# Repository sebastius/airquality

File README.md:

# airquality
A module based air quality sensor

Will feature
* ESP32
* BME280 for temperature, relative humidity and pressure
* PMS7003 for PM2.5 particles
* MH-Z19 for CO2

(and will strive for expandability with several standarized connectors)

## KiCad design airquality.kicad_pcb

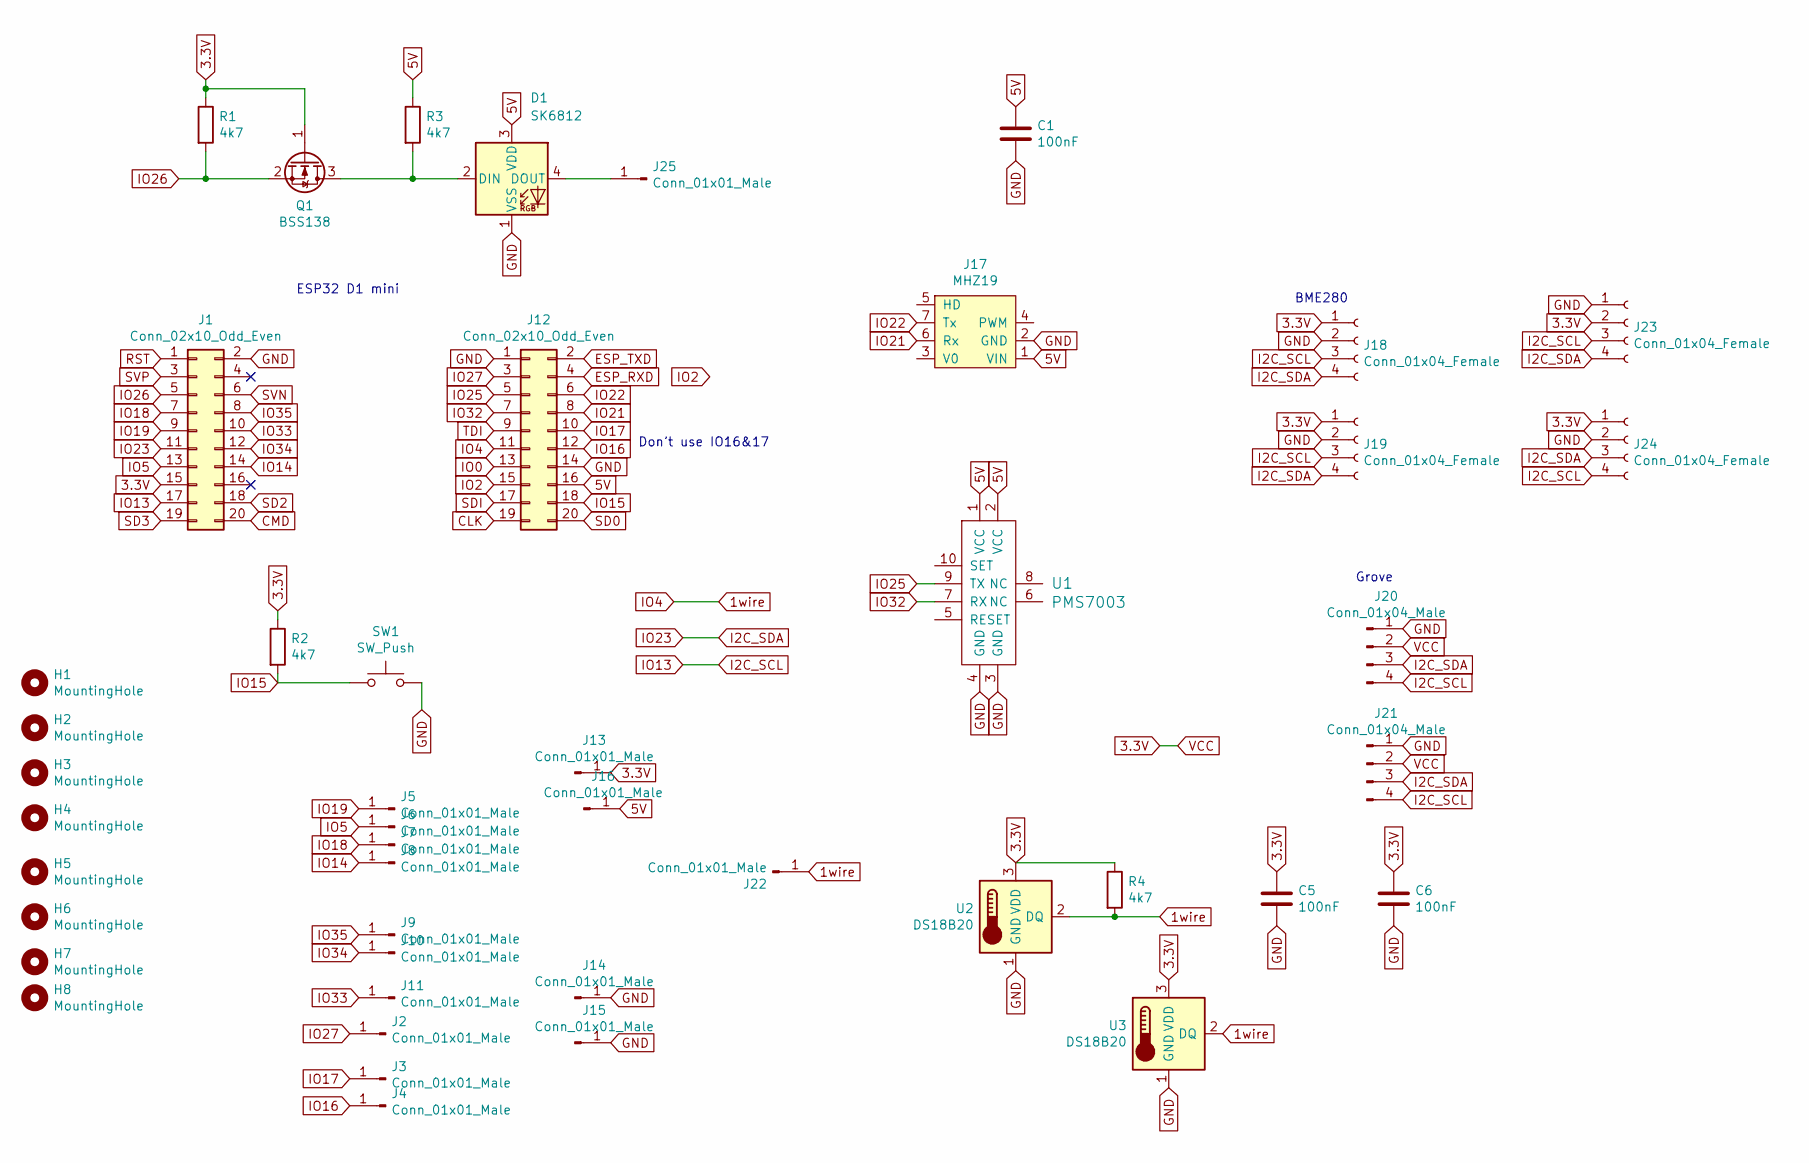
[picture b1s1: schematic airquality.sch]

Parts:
C1, C5, C6: 100nF; C_0805_2012Metric_Pad1.15x1.40mm_HandSolder
D1: SK6812; LED_SK6812_PLCC4_5.0x5.0mm_P3.2mm
H1, H2: MountingHole; MountingHole_4.3mm_M4
H3, H4: MountingHole; keyhole
H5, H6, H7, H8: MountingHole; MountingHole_3.2mm_M3
J1, J12: Conn_02x10_Odd_Even; PinSocket_2x10_P2.54mm_Vertical
J2, J3, J4, J5, J6, J7, J8, J9, J10, J11, J13, J14, J15, J16, J22, J25: Conn_01x01_Male; PinHeader_1x01_P2.54mm_Vertical
J17: MHZ19; Sensor_MH-Z19
J18, J19, J23, J24: Conn_01x04_Female; PinSocket_1x04_P2.54mm_Vertical
J20, J21: Conn_01x04_Male; JST_PH_S4B-PH-K_1x04_P2.00mm_Horizontal
Q1: BSS138; SOT-23
R1, R2, R3, R4: 4k7; R_0805_2012Metric_Pad1.15x1.40mm_HandSolder
SW1: SW_Push; SW_SPST_TL3342
U1: PMS7003
U2, U3: DS18B20; TO-92_Inline

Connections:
1wire: J12.11, J22.1, R4.2, U2.2 (DQ), U3.2 (DQ)
3.3V: C5.1, C6.1, J1.15, J13.1, J18.1, J19.1, J20.2, J21.2, J23.2, J24.1, Q1.1 (G), R1.1, R2.1, R4.1, U2.3 (VDD), U3.3 (VDD)
5V: C1.1, D1.3 (VDD), J12.16, J16.1, J17.1 (VIN), R3.1, U1.1 (VCC), U1.2 (VCC)
CLK: J12.19
CMD: J1.20
ESP_RXD: J12.4
ESP_TXD: J12.2
GND: C1.2, C5.2, C6.2, D1.1 (VSS), J1.2, J12.1, J12.14, J14.1, J15.1, J17.2 (GND), J18.2, J19.2, J20.1, J21.1, J23.1, J24.2, SW1.2, U1.3 (GND), U1.4 (GND), U2.1 (GND), U3.1 (GND)
I2C_SCL: J1.17, J18.3, J19.3, J20.4, J21.4, J23.3, J24.4
I2C_SDA: J1.11, J18.4, J19.4, J20.3, J21.3, J23.4, J24.3
IO0: J12.13
IO2: J12.15
IO5: J1.13, J6.1
IO14: J1.14, J8.1
IO15: J12.18, R2.2, SW1.1
IO16: J4.1, J12.12
IO17: J3.1, J12.10
IO18: J1.7, J7.1
IO19: J1.9, J5.1
IO21: J12.8, J17.6 (Rx)
IO22: J12.6, J17.7 (Tx)
IO25: J12.5, U1.9 (TX)
IO26: J1.5, Q1.2 (S), R1.2
IO27: J2.1, J12.3
IO32: J12.7, U1.7 (RX)
IO33: J1.10, J11.1
IO34: J1.12, J10.1
IO35: J1.8, J9.1
unnamed: D1.2 (DIN), Q1.3 (D), R3.2
unnamed: D1.4 (DOUT), J25.1
RST: J1.1
SD0: J12.20
SD2: J1.18
SD3: J1.19
SDI: J12.17
SVN: J1.6
SVP: J1.3
TDI: J12.9

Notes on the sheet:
ESP32 D1 mini
Grove
BME280
Don’t use IO16&17

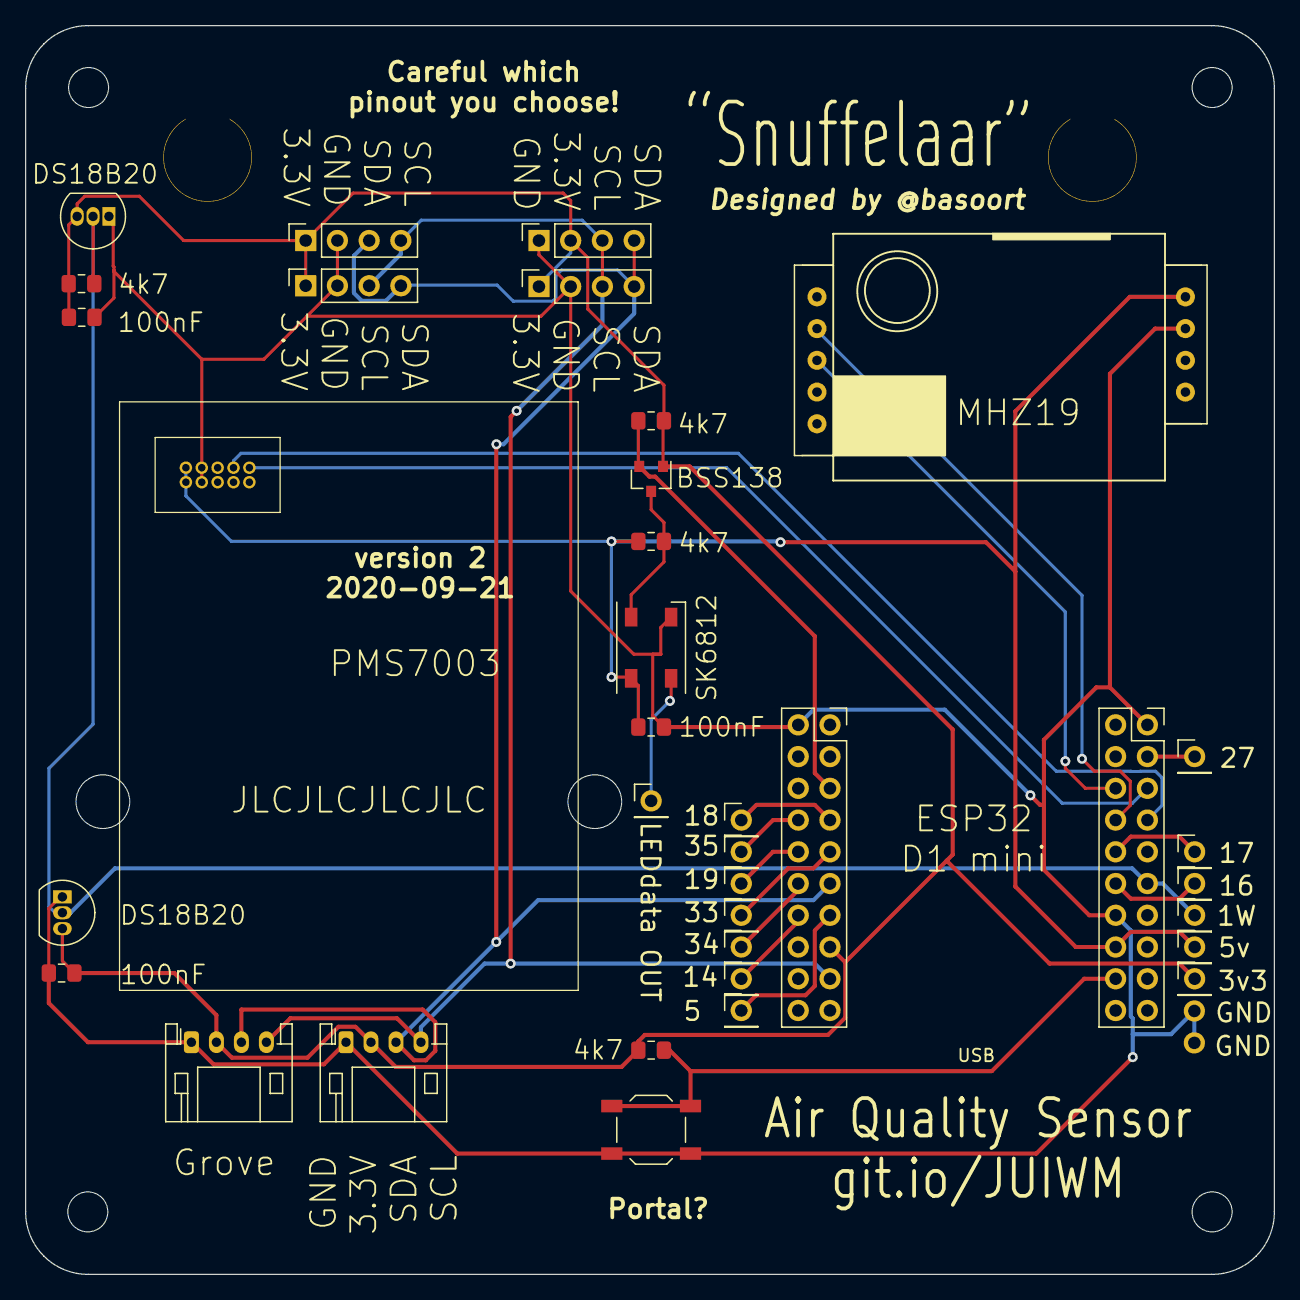
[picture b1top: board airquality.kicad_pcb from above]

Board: 2 copper layers, 99.9 x 99.9 mm, 46 parts (0 on the bottom side), 24 nets.

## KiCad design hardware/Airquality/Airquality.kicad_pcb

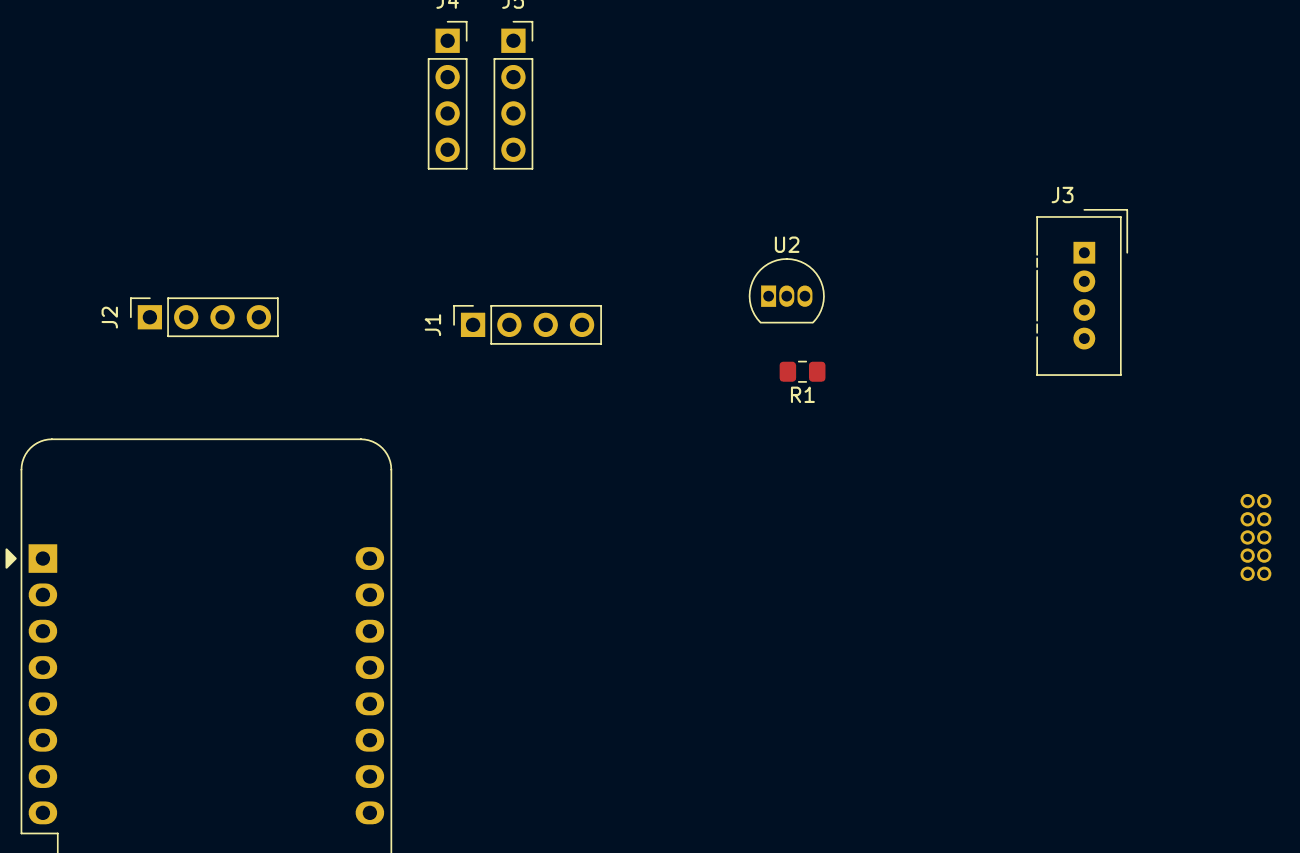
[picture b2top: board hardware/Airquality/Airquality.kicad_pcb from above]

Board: 2 copper layers, 9 parts (0 on the bottom side), 6 nets, no tracks yet.

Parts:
J1, J2, J4, J5: Conn_01x04_Female; PinSocket_1x04_P2.54mm_Vertical
J3: Conn_01x04_Male; NS-Tech_Grove_1x04_P2mm_Vertical
R1: 4K7; R_0805_2012Metric_Pad1.15x1.40mm_HandSolder
U1: WeMos_D1_mini; WEMOS_D1_mini_light
U2: DS18B20; TO-92_Inline
U3: PMS7003

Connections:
1wire: R1.2, U2.2
+3V3: J1.1, J2.1, J3.3, J4.1, J5.1, R1.1, U1.8, U2.3
+5V: U1.9, U3.1, U3.2
GND: J1.2, J2.2, J3.4, J4.2, J5.2, U1.10, U2.1, U3.3, U3.4
SCL: J1.3, J2.3, J3.1, J4.3, J5.3, U1.14
SDA: J1.4, J2.4, J3.2, J4.4, J5.4, U1.13

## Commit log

2020-06-01 wemos d1 mini submodule
2020-06-01 added some sensors and 3d models
2020-06-01 added 4 pinheaders for aliexpress i2c sensor modules
2020-08-19 cleanup and redo from start
2020-08-19 remove .dsstore from everywhere
2020-08-19 updated gitignore
2020-08-19 blank kicad
2020-08-27 version 1 done
2020-08-27 minor silkscreen edit for jlcpcb
2020-10-31 rev2
2023-06-07 Delete badgeconcept.svg
    Shouldn't be here.
